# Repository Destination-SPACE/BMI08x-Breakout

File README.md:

# BMI08x-Breakout

This breakout board is for the Bosch BMI085 & BMI088 6-axis Inertial Measurment Unit. This sensor has a triaxial gyroscope and a triaxial accelerometer. This sensor has default I2C addresses of 0x19 for the accelerometer and 0x69 for the gyroscope. This device is **3.3V only**.

Requires symbols and footprints from [DS Global Library](https://github.com/Destination-SPACE/DS-KiCad-Global-Source)

# Licnese

Licensed under the CERN OHLv2 - [Permissive](https://github.com/Destination-SPACE/BMI088-Breakout/blob/main/LICENSE) or as referenced.

(c) Destination SPACE Inc. 2022

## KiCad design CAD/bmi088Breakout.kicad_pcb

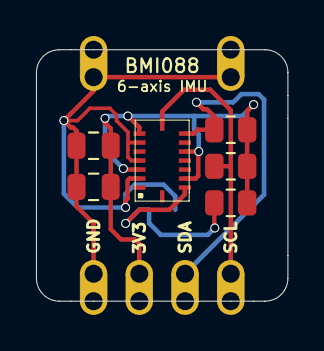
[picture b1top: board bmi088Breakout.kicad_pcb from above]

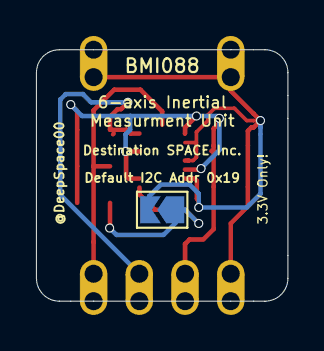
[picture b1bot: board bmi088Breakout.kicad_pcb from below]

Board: 2 copper layers, 14.0 x 14.0 mm, 10 parts (2 on the bottom side), 5 nets.

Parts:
C1, C2: 0.1uF; C_0805_2012Metric
J1: Castellated_Conn_01x04; Castellated_PinHeader_01x04_P2.54mm_Vertical
J2, J3: Castellated_Conn_01x01; Castellated_PinHeader_01x01_P2.54mm_Vertical
JP1: Jumper; SolderJumper-2_P1.3mm_Open_TrianglePad1.0x1.5mm
R1, R3: 4.7k; R_0805_2012Metric
R2: 4..7k; R_0805_2012Metric
U1: BMI088

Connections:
+3V3: C1.1, C2.1, J1.2, R1.2, R2.1, R3.1, U1.3, U1.7, U1.11, U1.14
GND: C1.2, C2.2, J1.1, J2.1, J3.1, JP1.2, U1.2, U1.4, U1.6
SCL: J1.4, R2.2, U1.8
SDA: J1.3, R3.2, U1.9
SDO1: JP1.1, R1.1, U1.15

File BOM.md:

| Designator | Package | Manufacturer | Manufacturer Part No | Supplier | Supplier Part No | Value | Other |
| ------------- | ------------- | ------------- | ------------- | ------------- | ------------- | ------------- | ------------- |
| U1 | 16-VFLGA | Bosch Sensortec | BMI088 | Digi-Key |  828-1082-1-ND |   |   | 
| C1 | 0805 | Samsung Electro-Mechanics | CL21B104KBCNNNC | Digi-Key | 1276-1003-1-ND | 0.1uF | 50V |
| C2 | 0805 | Samsung Electro-Mechanics | CL21B104KBCNNNC | Digi-Key | 1276-1003-1-ND | 0.1uF | 50V |
| R1 | 0805 | Panasonic Electronic Components | ERA-6AEB472V | Digi-Key | P4.7KDACT-ND | 4.7k | 0.125W |
| R2 | 0805 | Panasonic Electronic Components | ERA-6AEB472V | Digi-Key | P4.7KDACT-ND | 4.7k | 0.125W |
| R3 | 0805 | Panasonic Electronic Components | ERA-6AEB472V | Digi-Key | P4.7KDACT-ND | 4.7k | 0.125W |

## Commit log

2021-09-21 Create LICENSE
2021-09-28 added castellated holes to board
2022-03-29 Rename CAD/bmi08xBreakout-cache.lib to CAD-files/bmi08xBreakout-cache.lib
2022-03-29 Rename CAD/bmi08xBreakout.kicad_pcb to CAD-files/bmi08xBreakout.kicad_pcb
2022-03-29 Rename CAD/bmi08xBreakout.kicad_pro to CAD-files/bmi08xBreakout.kicad_pro
2022-03-29 Rename CAD/bmi08xBreakout.kicad_sch to CAD-files/bmi08xBreakout.kicad_sch
